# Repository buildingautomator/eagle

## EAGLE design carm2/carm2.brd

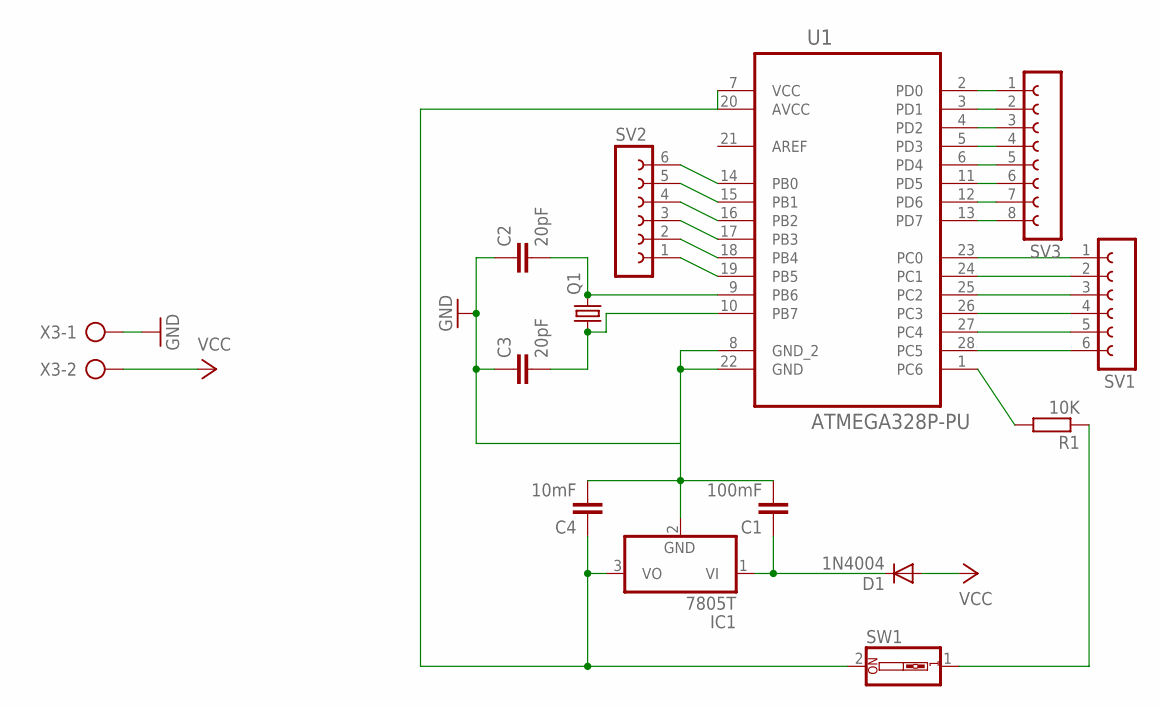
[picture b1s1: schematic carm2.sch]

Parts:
C1: 100mF; C10B4
C2, C3: 20pF; C10B4
C4: 10mF; C10B4
D1: 1N4004; DO41-10
IC1: 7805T; TO220H
Q1: CRYSTALHC49S; HC49/S
R1: 10K; 0207/10
SV1, SV2: FE06-1; FE06
SV3: FE08-1; FE08
SW1: SW_DIP-1; EDG-01
U1: ATMEGA328P-PU; DIP254P762X457-28
X3: AK300/2

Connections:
GND: C1.2, C2.1, C3.1, C4.2, IC1.2 (GND), U1.8 (GND_2), U1.22 (GND), X3.1
unnamed: R1.2, U1.1 (PC6)
unnamed: R1.1, SW1.1
unnamed: SV3.1, U1.2 (PD0)
unnamed: SV3.2, U1.3 (PD1)
unnamed: SV3.3, U1.4 (PD2)
unnamed: SV3.4, U1.5 (PD3)
unnamed: SV3.5, U1.6 (PD4)
unnamed: SV3.6, U1.11 (PD5)
unnamed: SV3.7, U1.12 (PD6)
unnamed: SV3.8, U1.13 (PD7)
unnamed: SV1.1, U1.23 (PC0)
unnamed: SV1.2, U1.24 (PC1)
unnamed: SV1.3, U1.25 (PC2)
unnamed: SV1.4, U1.26 (PC3)
unnamed: SV1.5, U1.27 (PC4)
unnamed: SV1.6, U1.28 (PC5)
unnamed: SV2.6, U1.14 (PB0)
unnamed: SV2.5, U1.15 (PB1)
unnamed: SV2.4, U1.16 (PB2)
unnamed: SV2.3, U1.17 (PB3)
unnamed: SV2.2, U1.18 (PB4)
unnamed: SV2.1, U1.19 (PB5)
unnamed: C2.2, Q1.2, U1.9 (PB6)
unnamed: C1.1, D1.C, IC1.1 (VI)
unnamed: C3.2, Q1.1, U1.10 (PB7)
VCC: D1.A, X3.2
VCC5: C4.1, IC1.3 (VO), SW1.2, U1.7 (VCC), U1.20 (AVCC)

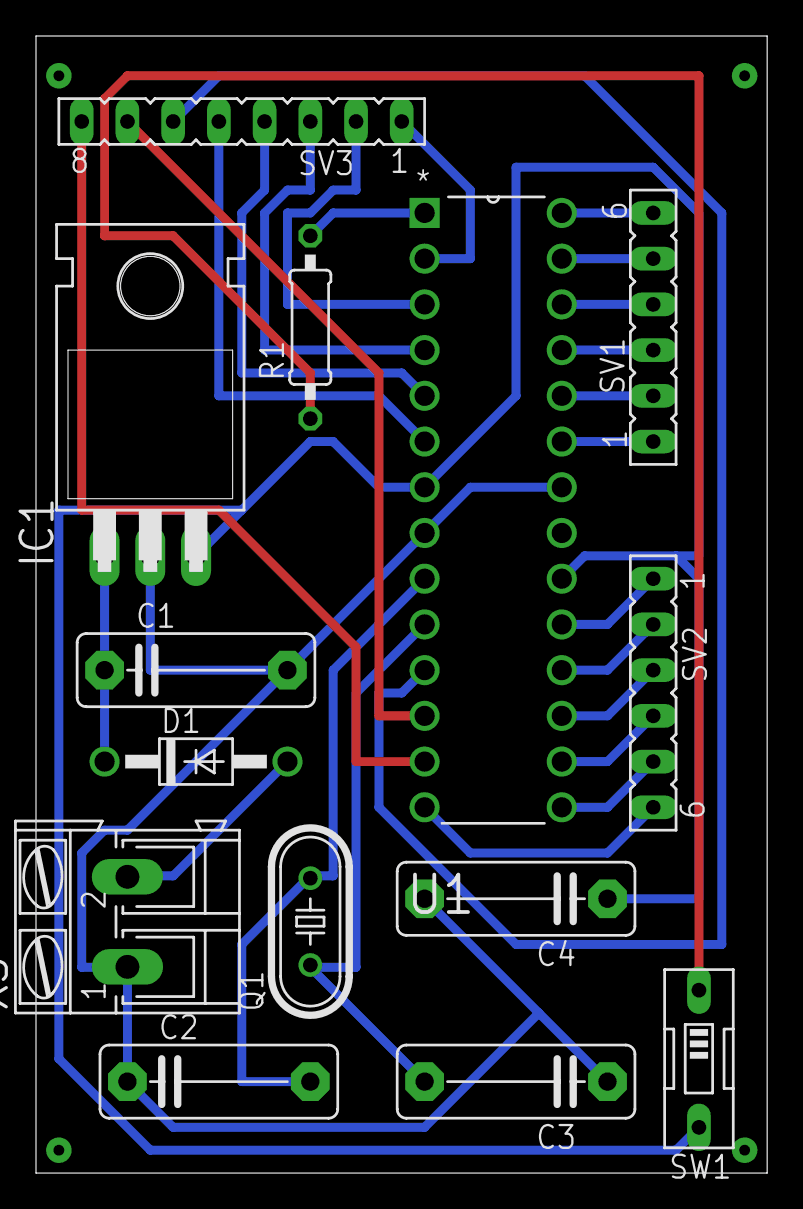
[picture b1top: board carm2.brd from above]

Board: 2 copper layers, 40.6 x 63.2 mm, 14 parts (0 on the bottom side), 28 nets.

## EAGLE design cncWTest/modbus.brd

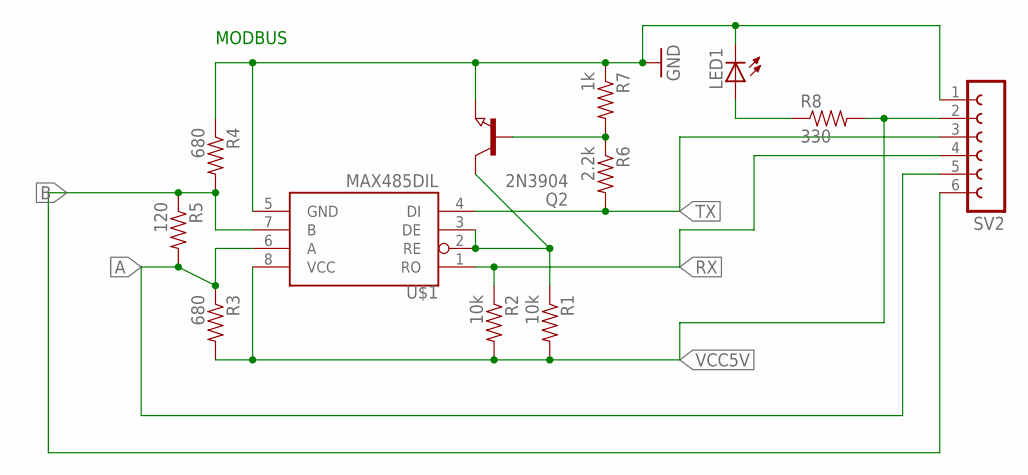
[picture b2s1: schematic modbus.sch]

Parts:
LED1: LEDCHIP-LED0805; CHIP-LED0805
Q2: 2N3904; SOT23
R1, R2: 10k; 0805
R3, R4: 680; 0805
R5: 120; 0805
R6: 2.2k; 0805
R7: 1k; 0805
R8: 330; 0805
SV2: FE06-1; FE06
U$1: MAX485DIL; DIL08

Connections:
A: R3.1, R5.2, SV2.5, U$1.6 (A)
B: R4.2, R5.1, SV2.6, U$1.7 (B)
GND: LED1.C, Q2.2 (E), R4.1, R7.1, SV2.1, U$1.5 (GND)
unnamed: LED1.A, R8.1
unnamed: Q2.3 (C), R1.1, U$1.2 (RE), U$1.3 (DE)
unnamed: Q2.1 (B), R6.1, R7.2
RX: R2.1, SV2.4, U$1.1 (RO)
TX: R6.2, SV2.3, U$1.4 (DI)
VCC5V: R1.2, R2.2, R3.2, R8.2, SV2.2, U$1.8 (VCC)

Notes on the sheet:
MODBUS

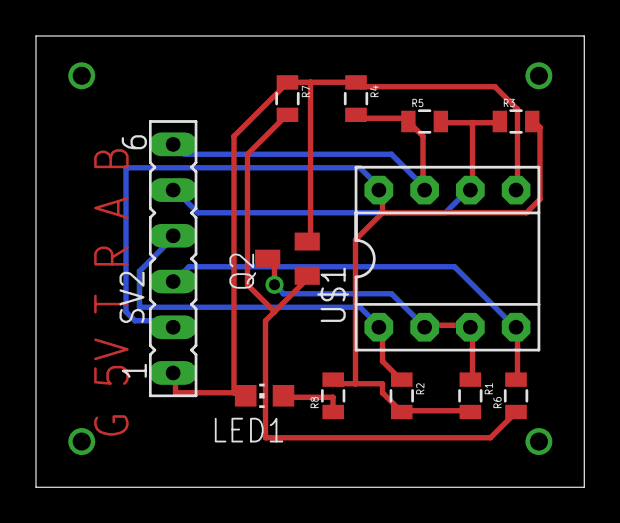
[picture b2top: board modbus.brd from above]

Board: 2 copper layers, 30.5 x 25.1 mm, 12 parts (0 on the bottom side), 9 nets.

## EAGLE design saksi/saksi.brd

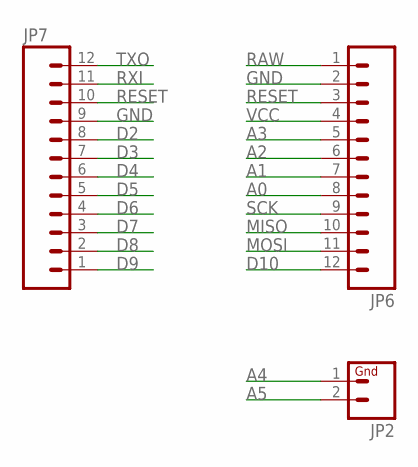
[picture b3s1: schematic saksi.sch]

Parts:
JP2: M02PTH; 1X02
JP6, JP7: M12PTH; 1X12

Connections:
A0: JP6.8
A1: JP6.7
A2: JP6.6
A3: JP6.5
A4: JP2.1
A5: JP2.2
D2: JP7.8
D3: JP7.7
D4: JP7.6
D5: JP7.5
D6: JP7.4
D7: JP7.3
D8: JP7.2
D9: JP7.1
D10: JP6.12
GND: JP6.2, JP7.9
MISO: JP6.10
MOSI: JP6.11
RAW: JP6.1
RESET: JP6.3, JP7.10
RXI: JP7.11
SCK: JP6.9
TXO: JP7.12
VCC: JP6.4

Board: 2 copper layers, 3 parts (3 on the bottom side), 2 nets, no tracks yet.

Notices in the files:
parts and their libraries:
SparkFun-Passives: Licensing: Creative Commons ShareAlike 4.0 International - https://creativecommons.org/licenses/by-sa/4.0
